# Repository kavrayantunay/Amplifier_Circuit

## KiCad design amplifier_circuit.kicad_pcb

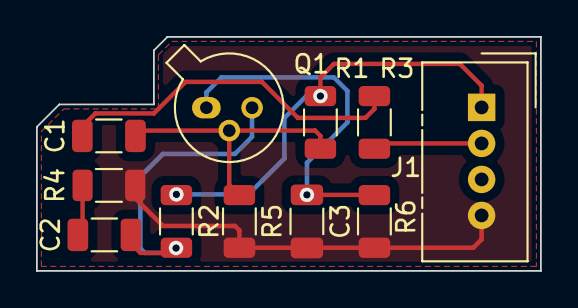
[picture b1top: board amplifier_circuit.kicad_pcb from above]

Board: 2 copper layers, 28.0 x 13.0 mm, 11 parts (0 on the bottom side), 8 nets.

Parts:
C1: 100nF; C_1206_3216Metric
C2: 220nF; C_1206_3216Metric
C3: 100uF; C_1206_3216Metric
J1: Conn_01x04; NS-Tech_Grove_1x04_P2mm_Vertical
Q1: BC107; TO-18-3
R1: 22k; R_1206_3216Metric
R2: 2.2k; R_1206_3216Metric
R3: 200; R_1206_3216Metric
R4, R5: 10k; R_1206_3216Metric
R6: 1k; R_1206_3216Metric

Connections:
/in: J1.2, R3.1
GND: C3.2, J1.4, R4.2, R5.2, R6.2
unnamed: C1.1, R3.2
unnamed: C1.2, Q1.2 (B), R1.2, R5.1
unnamed: C2.1, Q1.3 (C), R2.2
unnamed: C2.2, R4.1
unnamed: C3.1, Q1.1 (E), R6.1
VCC: J1.1, R1.1, R2.1
